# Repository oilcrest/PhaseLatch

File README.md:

# PhaseLatch

PhaseLatch – 6502-Interfaced High-Speed ADC for Experimental SDR

PhaseLatch is an open-source hardware project that explores how far a classic MOS 6502-class CPU can be pushed into modern signal-processing territory. The board implements a dual-channel, 10-bit, 20 MSPS analog-to-digital converter with a straight binary parallel output, allowing the ADC to be memory-mapped directly onto a 6502 (8 bit) data bus.

Unlike typical SDR designs that rely on high-performance microcontrollers or FPGAs, PhaseLatch intentionally interfaces high-speed conversion hardware with a severely resource-constrained 8-bit CPU. This makes it a platform for experimenting with timing limits, bus contention, memory expansion, and minimalist DSP techniques such as Goertzel tone detection executed entirely on the 6502.

The board is designed as a modular Arduino-shield-style form factor and is intended to stack with the PhaseLoom IQ mixer and the 65uino 6502 system. Direct access to the CPU address, data, and control signals enables single-instruction ADC reads and deterministic sampling under software control.

PhaseLatch is not intended to achieve full theoretical ADC bandwidth on a 6502. Instead, it serves as a practical exploration of real-world limitations, architectural trade-offs, and creative signal-processing approaches on vintage computing hardware.

## Purchase

Interested in owning a PhaseLatch?  
[Buy one here](https://www.imania.dk/index.php?cPath=204&sort=5a&language=en).

## How to Use
[6502 source code still lives over on the 65uino project](https://github.com/AndersBNielsen/65uino/)

The main 65uino firmware currently comes with support for the PhaseLatch built in. Time of writing, use the SDR branch. 

To get the full bandwidth out of PhaseLatch, it can also be used with an **FX2LP** USB streaming board instead of the **65uino**.

## Software
The `software/` folder contains the USB streamer firmware + host-side tools for getting PhaseLatch data into SDR software.

- [software/README.md](software/README.md): Overview, build instructions, and a demo cheat sheet.
- [software/firmware/](software/firmware/): FX2/FX2LP firmware (USB streaming).
- [software/host/](software/host/): Host utilities (USB reader, format conversion, DC / IQ correction).
- [software/examples/](software/examples/): Example pipelines (including streaming to `/tmp/iq.fifo` for Gqrx).
- [software/doc/](software/doc/): Notes on wiring and rate planning.

## Using with an FX2LP (USB streaming)
PhaseLatch includes header footprints intended for wiring to an **FX2LP** dev board. The FX2LP provides USB 2.0 high‑speed bulk streaming and acts as the “bridge” from the ADC to a host PC.

At a high level the flow is:
- FX2LP firmware streams raw samples over USB
- host reads via libusb and converts to CF32
- stream is written to `/tmp/iq.fifo` so **Gqrx** can open it

Start with the guide in `software/README.md`, then use `software/examples/pipeline.sh` for a one-command stream to `/tmp/iq.fifo`.

## Getting a PCB

## Production & Manufacturing
- The `jlcpcb/gerber/` folder contains all necessary files for PCB fabrication.
- The `production_files/` folder includes:
  - `BOM-PhaseLatch.csv`: Bill of Materials
  - `CPL-PhaseLatch.csv`: Component Placement List
  - `GERBER-PhaseLatch.zip`: Zipped Gerber files for easy upload

This project is kindly sponsored by JLCPCB. They offer cheap, professional looking PCBs and super fast delivery.

Step 1: Get the gerber file zip package from the /hardware folder

Step 2: Upload to JLCPCB [https://jlcpcb.com/?from=Anders_N](https://jlcpcb.com/?from=Anders_N)

Step 3: Pick your color, surface finish and order.

You can use these affiliate links to get a board for $2 and also get $54 worth of New User Coupons at: https://jlcpcb.com/?from=Anders_N

And in case you also want to order a 3D-printed case you can use this link. 
How to Get a $7 3D Printing Coupon: [https://3d.jlcpcb.com/?from=Anders3DP](https://jlc3dp.com/?from=Anders_N)

---

For more details, technical explanations, and the full story behind PhaseLoom, check out the project video and documentation. Special thanks to JLCPCB and Fnirsi for supporting the development of this project!

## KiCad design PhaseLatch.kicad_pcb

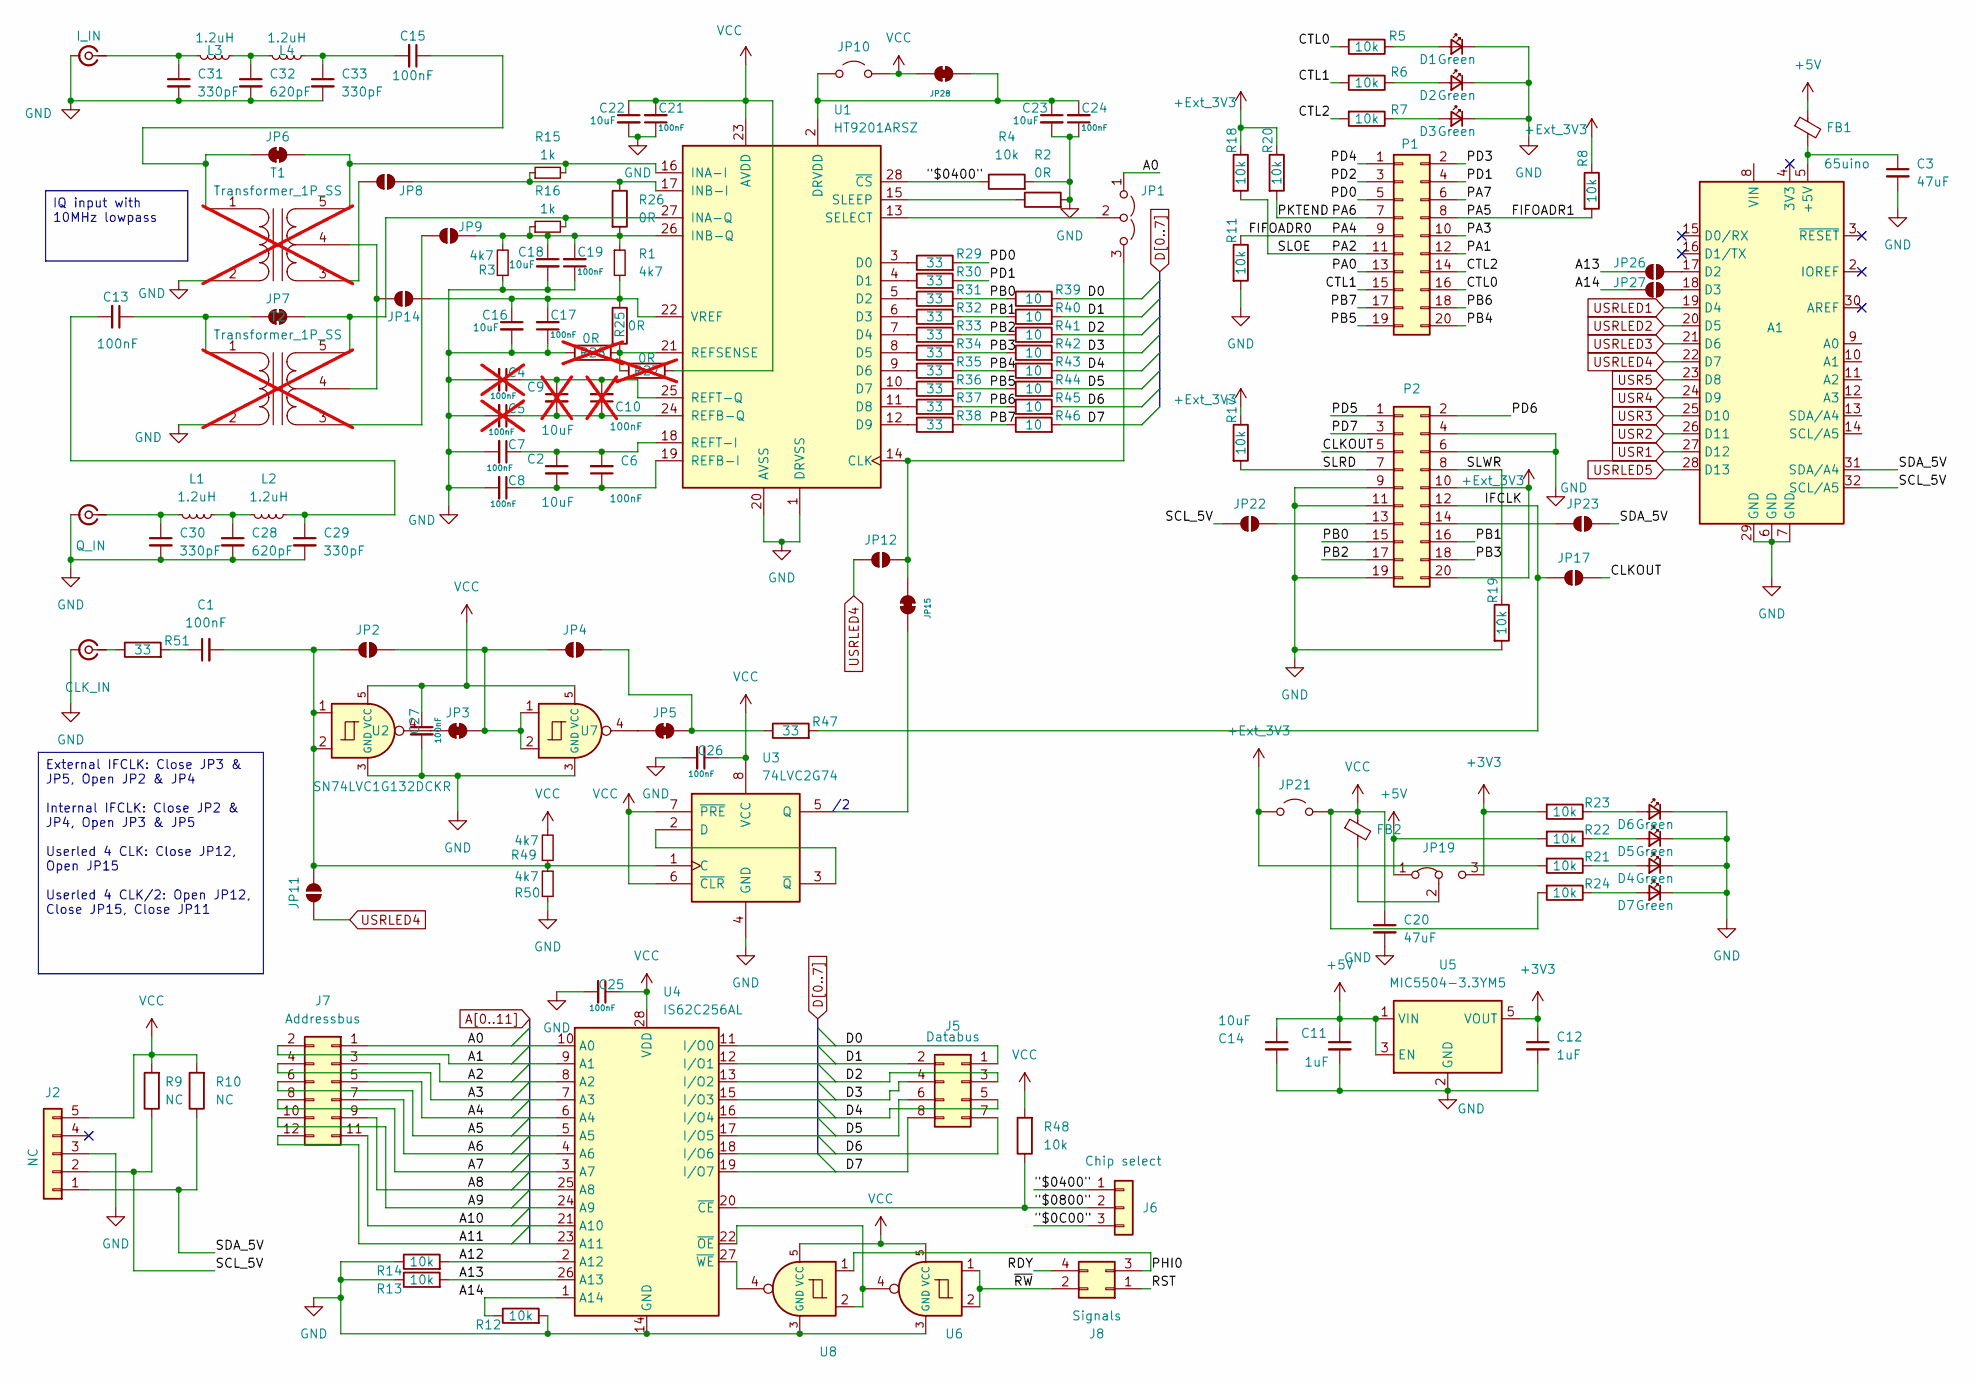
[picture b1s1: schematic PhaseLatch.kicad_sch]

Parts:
A1: 65uino; Arduino_UNO_R3
C1, C6, C7, C8, C13, C15, C17, C19, C21, C24, C25, C26, C27: 100nF; C_0402_1005Metric; LCSC C1525
C2, C14, C16, C18, C22, C23: 10uF; C_0603_1608Metric; LCSC C96446
C3, C20: 47uF; C_1206_3216Metric; LCSC C96123
C4, C5, C10: 100nF; C_0402_1005Metric; LCSC C1525; not fitted
C9: 10uF; C_0603_1608Metric; LCSC C96446; not fitted
C11, C12: 1uF; C_0805_2012Metric; LCSC C28323
C28, C32: 620pF; C_0402_1005Metric; LCSC C415543
C29, C30, C31, C33: 330pF; C_0402_1005Metric; LCSC C2177105
D1, D2, D3, D4, D5, D6, D7: Green; LED_0805_2012Metric; LCSC C2297
FB1, FB2: FerriteBead_Small; L_0603_1608Metric; LCSC C14709
J2: NC; PinHeader_1x05_P2.54mm_Vertical
J5: Databus; PinHeader_2x04_P2.54mm_Vertical
J6: Chip select; PinSocket_1x03_P2.54mm_Vertical
J7: Addressbus; PinHeader_2x06_P2.54mm_Vertical
J8: Signals; PinHeader_2x02_P2.54mm_Vertical
J20: I_IN; SMA_Samtec_SMA-J-P-H-ST-EM1_EdgeMount; LCSC C5301850
J21: Q_IN; SMA_Samtec_SMA-J-P-H-ST-EM1_EdgeMount; LCSC C5301850
J23: CLK_IN; SMA_Samtec_SMA-J-P-H-ST-EM1_EdgeMount; LCSC C5301850
JP1: Jumper_3_Open; PinHeader_1x03_P2.54mm_Vertical
JP2, JP4, JP8, JP9, JP11, JP12, JP14, JP17, JP22, JP23, JP26, JP27: SolderJumper_2_Open; SolderJumper-2_P1.3mm_Open_RoundedPad1.0x1.5mm
JP3, JP5, JP6, JP7, JP15, JP28: SolderJumper-2_P1.3mm_Bridged_RoundedPad1.0x1.5mm
JP10, JP21: Jumper_2_Open; PinHeader_1x02_P2.54mm_Vertical
JP19: Jumper_3_Bridged12; PinHeader_1x03_P2.54mm_Vertical
L1, L2, L3, L4: 1.2uH; L_0603_1608Metric; LCSC C393979
P1, P2: Conn_02x10_Odd_Even; PinSocket_2x10_P2.54mm_Vertical
R1, R3, R49, R50: 4k7; R_0402_1005Metric; LCSC C25900
R2, R25, R26: 0R; R_0402_1005Metric
R4, R5, R6, R7, R8, R11, R12, R13, R14, R17, R18, R19, R20, R21, R22, R23, R24, R48: 10k; R_0402_1005Metric; LCSC C25744
R9, R10: NC; R_0603_1608Metric
R15, R16: 1k; R_0402_1005Metric; LCSC C11702
R27, R28: 0R; R_0402_1005Metric; not fitted
R29, R30, R31, R32, R33, R34, R35, R36, R37, R38, R47, R51: 33; R_0402_1005Metric; LCSC C25105
R39, R40, R41, R42, R43, R44, R45, R46: 10; R_0402_1005Metric; LCSC C25077
T1, T2: Transformer_1P_SS; Transformer_MiniCircuits_AT224-1A-AltPinout; not fitted
U1: HT9201ARSZ; SSOP-28_5.3x10.2mm_P0.65mm; LCSC C3019546
U2, U6, U7, U8: SN74LVC1G132DCKR; SOT-23-5; LCSC C49188130
U3: 74LVC2G74; VSSOP-8_2.3x2mm_P0.5mm; LCSC C70285
U4: IS62C256AL; TSOP-I-28_11.8x8mm_P0.55mm; LCSC C47143
U5: MIC5504-3.3YM5; SOT-23-5; LCSC C3021093

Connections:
+3V3: C12.1, JP19.3 (B), R23.2, U5.5 (VOUT)
+5V: C11.1, C14.1, FB1.1, JP19.1 (A), R22.2, U5.1 (VIN), U5.3 (EN)
+Ext_3V3: JP21.1 (A), P2.10, P2.20, R8.1, R17.1, R18.1, R20.1, R21.2
/"$0C00": J6.3
/"$0400": J6.1, R4.1, U1.28 (~CS)
/"$0800": J6.2, R48.1, U4.20 (~CE)
/A12: R14.2, U4.2 (A12)
/A13: JP26.1 (A), R13.2, U4.26 (A13)
/A14: JP27.1 (A), R12.1, U4.1 (A14)
/CLKOUT: JP17.2 (B), P2.5
/CTL0: P1.16, R5.2
/CTL1: P1.15, R6.2
/CTL2: P1.14, R7.2
/FIFOADR0: P1.9, R11.1
/FIFOADR1: P1.8, R8.2
/IFCLK: JP17.1 (A), P2.12, R47.2
/PA0: P1.13
/PA1: P1.12
/PA2: P1.11, R18.2
/PA3: P1.10
/PA6: P1.7, R20.2
/PA7: P1.6
/PB0: P2.15, R31.2, R39.1
/PB1: P2.16, R32.2, R40.1
/PB2: P2.17, R33.2, R41.1
/PB3: P2.18, R34.2, R42.1
/PB4: P1.20, R35.2, R43.1
/PB5: P1.19, R36.2, R44.1
/PB6: P1.18, R37.2, R45.1
/PB7: P1.17, R38.2, R46.1
/PD0: P1.5, R29.2
/PD1: P1.4, R30.2
/PD2: P1.3
/PD3: P1.2
/PD4: P1.1
/PD5: P2.1
/PD6: P2.2
/PD7: P2.3
/PHI0: J8.3, U8.1
/RDY: J8.4
/RST: J8.1
/SCL_5V: A1.32 (SCL/A5), J2.2, JP22.1 (A), R9.1
/SDA_5V: A1.31 (SDA/A4), J2.1, JP23.2 (B), R10.1
/SLRD: P2.7, R17.2
/SLWR: P2.8, R19.1
/~RW: J8.2, U6.1, U6.2
A0: J7.1, JP1.1 (A), U4.10 (A0)
A1: J7.2, U4.9 (A1)
A2: J7.3, U4.8 (A2)
A3: J7.4, U4.7 (A3)
A4: J7.5, U4.6 (A4)
A5: J7.6, U4.5 (A5)
A6: J7.7, U4.4 (A6)
A7: J7.8, U4.3 (A7)
A8: J7.9, U4.25 (A8)
A9: J7.10, U4.24 (A9)
A10: J7.11, U4.21 (A10)
A11: J7.12, U4.23 (A11)
D0: J5.1, R39.2, U4.11 (I/O0)
D1: J5.2, R40.2, U4.12 (I/O1)
D2: J5.3, R41.2, U4.13 (I/O2)
D3: J5.4, R42.2, U4.15 (I/O3)
D4: J5.5, R43.2, U4.16 (I/O4)
D5: J5.6, R44.2, U4.17 (I/O5)
D6: J5.7, R45.2, U4.18 (I/O6)
D7: J5.8, R46.2, U4.19 (I/O7)
GND: A1.6 (GND), A1.7 (GND), A1.29 (GND), C3.2, C4.2, C5.2, C7.2, C8.2, C11.2, C12.2, C14.2, C16.2, C17.1, C18.2, C19.1, C20.2, C21.1, C22.2, C23.2, C24.1, C25.2, C26.2, C27.2, C28.2, C29.2, C30.2, C31.2, C32.2, C33.2, D1.1 (K), D2.1 (K), D3.1 (K), D4.1 (K), D5.1 (K), D6.1 (K), D7.1 (K), J2.3, J20.2 (Ext), J21.2 (Ext), J23.2 (Ext), P2.4, P2.6, P2.9, P2.11, P2.19, R2.2, R3.1, R4.2, R11.2, R12.2, R13.1, R14.1, R19.2, R28.1, R50.1, T1.2 (AB), T2.2 (AB), U1.1 (DRVSS), U1.20 (AVSS), U2.3 (GND), U3.4 (GND), U4.14 (GND), U5.2 (GND), U6.3 (GND), U7.3 (GND), U8.3 (GND)
unnamed: A1.5 (+5V), C3.1, FB1.2
unnamed: A1.17 (D2), JP26.2 (B)
unnamed: A1.18 (D3), JP27.2 (B)
unnamed: C1.1, R51.2
unnamed: C13.2, C29.1, L2.1
unnamed: C15.2, C33.1, L4.1
unnamed: C28.1, L1.1, L2.2
unnamed: C32.1, L3.1, L4.2
unnamed: D1.2 (A), R5.1
unnamed: D2.2 (A), R6.1
unnamed: D3.2 (A), R7.1
unnamed: D4.2 (A), R21.1
unnamed: D5.2 (A), R22.1
unnamed: D6.2 (A), R23.1
unnamed: D7.2 (A), R24.1
unnamed: C31.1, J20.1 (In), L3.2
unnamed: C30.1, J21.1 (In), L1.2
unnamed: J23.1 (In), R51.1
unnamed: JP1.3 (B), JP12.2 (B), JP15.2 (B), U1.14 (CLK)
unnamed: JP1.2 (C), U1.13 (SELECT)
unnamed: JP2.2 (B), JP3.2 (B), JP4.1 (A), U7.1, U7.2
unnamed: JP3.1 (A), U2.4
unnamed: JP4.2 (B), JP5.2 (B), R47.1
unnamed: JP5.1 (A), U7.4
unnamed: C15.1, JP6.1 (A), T1.1 (AA)
unnamed: JP6.2 (B), R15.2, T1.5 (SB), U1.16 (INA-I)
unnamed: C13.1, JP7.1 (A), T2.1 (AA)
unnamed: JP7.2 (B), R16.2, T2.5 (SB), U1.27 (INA-Q)
unnamed: JP8.1 (A), R15.1, R26.1, U1.17 (INB-I)
unnamed: JP8.2 (B), T1.3 (SA)
unnamed: C18.1, C19.2, JP9.1 (A), R1.1, R3.2, R16.1, R26.2, U1.26 (INB-Q)
unnamed: JP9.2 (B), T2.3 (SA)
unnamed: C23.1, C24.2, JP10.1 (A), JP28.2 (B), U1.2 (DRVDD)
unnamed: C1.2, JP2.1 (A), JP11.2 (B), R49.1, R50.2, U2.1, U2.2, U3.1 (C)
unnamed: C16.1, C17.2, JP14.1 (A), R1.2, R25.1, U1.22 (VREF)
unnamed: JP14.2 (B), T1.4 (SC), T2.4 (SC)
unnamed: JP15.1 (A), U3.5 (Q)
unnamed: FB2.2, JP19.2 (C)
unnamed: JP22.2 (B), P2.13
unnamed: JP23.1 (A), P2.14
unnamed: R29.1, U1.3 (D0)
unnamed: R30.1, U1.4 (D1)
unnamed: R31.1, U1.5 (D2)
unnamed: R32.1, U1.6 (D3)
unnamed: R33.1, U1.7 (D4)
unnamed: R34.1, U1.8 (D5)
unnamed: R35.1, U1.9 (D6)
unnamed: R36.1, U1.10 (D7)
unnamed: R37.1, U1.11 (D8)
unnamed: R38.1, U1.12 (D9)
unnamed: C2.2, C6.1, C8.1, U1.19 (REFB-I)
unnamed: C5.1, C9.2, C10.1, U1.24 (REFB-Q)
unnamed: R25.2, R27.1, R28.2, U1.21 (REFSENSE)
unnamed: C2.1, C6.2, C7.1, U1.18 (REFT-I)
unnamed: C4.1, C9.1, C10.2, U1.25 (REFT-Q)
unnamed: R2.1, U1.15 (SLEEP)
unnamed: U3.2 (D), U3.3 (~Q)
unnamed: U4.22 (~OE), U6.4, U8.2
unnamed: U4.27 (~WE), U8.4
USR1: A1.27 (D12)
USR2: A1.26 (D11)
USR3: A1.25 (D10)
USR4: A1.24 (D9)
USR5: A1.23 (D8)
USRLED1: A1.19 (D4)
USRLED2: A1.20 (D5)
USRLED3: A1.21 (D6)
USRLED4: A1.22 (D7), JP11.1 (A), JP12.1 (A)
USRLED5: A1.28 (D13)
VCC: C20.1, C21.2, C22.1, C25.1, C26.1, C27.1, FB2.1, J2.5, JP10.2 (B), JP21.2 (B), JP28.1 (A), R9.2, R10.2, R24.2, R27.2, R48.2, R49.2, U1.23 (AVDD), U2.5 (VCC), U3.6 (~CLR), U3.7 (~PRE), U3.8 (VCC), U4.28 (VDD), U6.5 (VCC), U7.5 (VCC), U8.5 (VCC)

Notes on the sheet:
IQ input with 10MHz lowpass
External IFCLK: Close JP3 & JP5, Open JP2 & JP4 Internal IFCLK: Close JP2 & JP4, Open JP3 & JP5 Userled 4 CLK: Close JP12, Open JP15 Userled 4 CLK/2: Open JP12, Close JP15, Close JP11

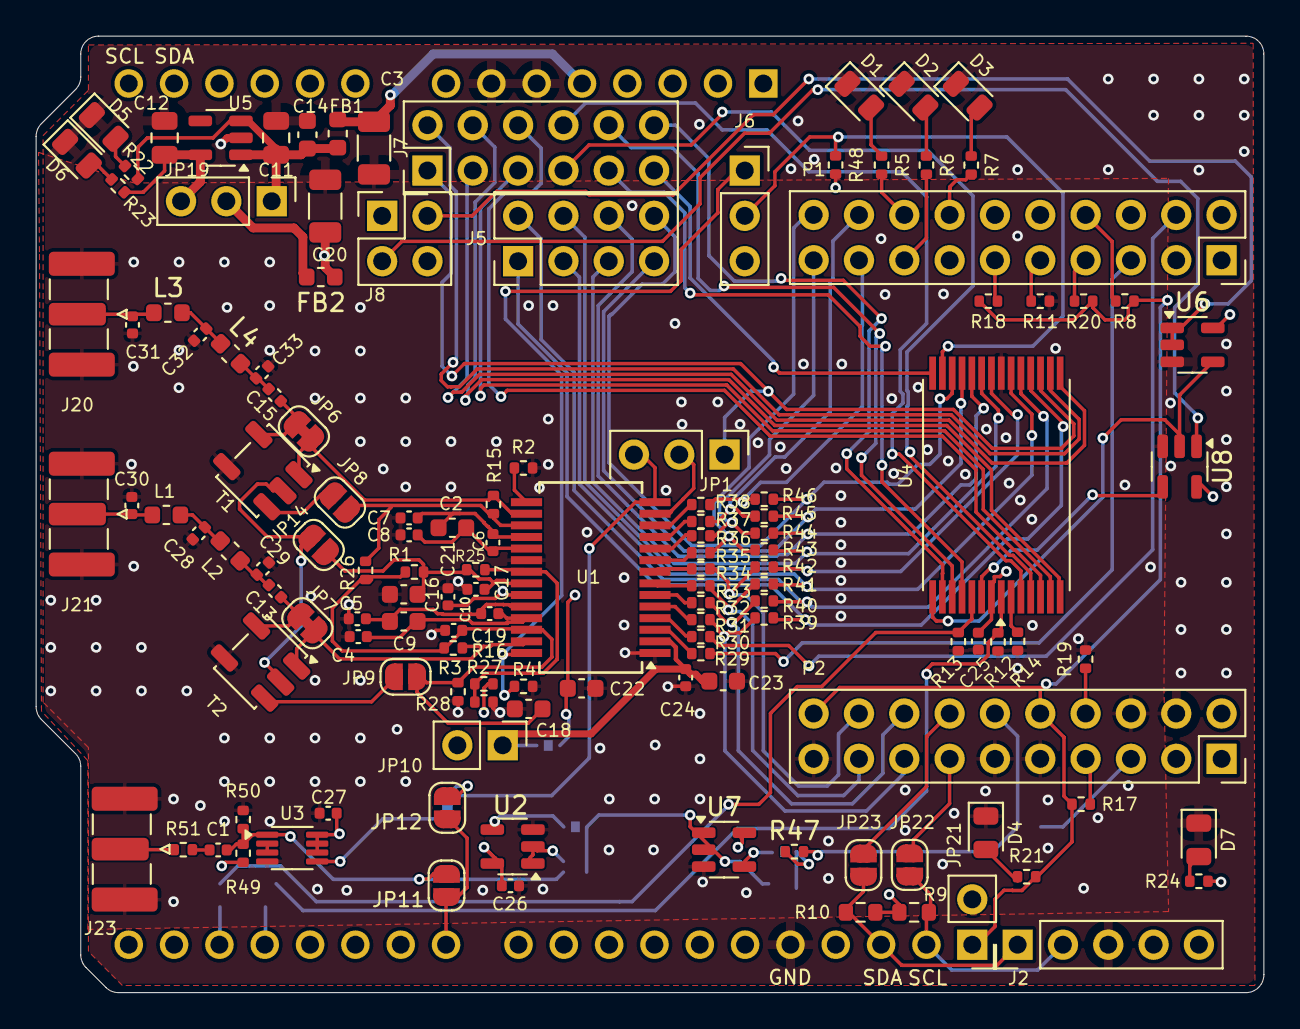
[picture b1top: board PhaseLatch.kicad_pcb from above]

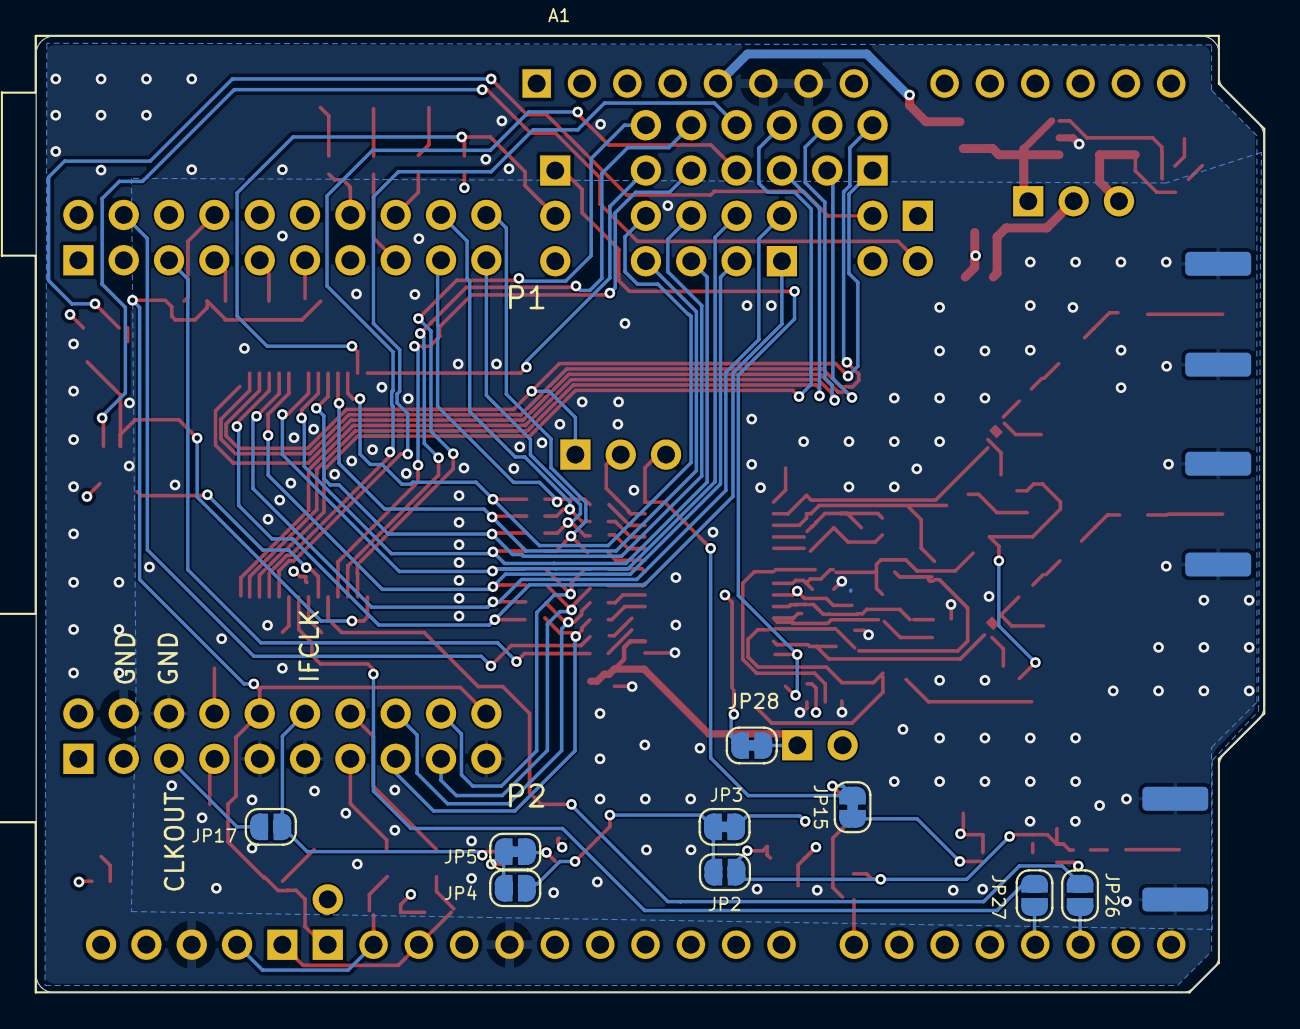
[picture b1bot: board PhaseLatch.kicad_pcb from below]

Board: 4 copper layers, 68.8 x 53.6 mm, 140 parts (10 on the bottom side), 115 nets.

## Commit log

2025-09-17 Series termination, fork resistors
2025-09-17 Routing
2026-03-14 IQ bias offset, IQ balancing, documentation
